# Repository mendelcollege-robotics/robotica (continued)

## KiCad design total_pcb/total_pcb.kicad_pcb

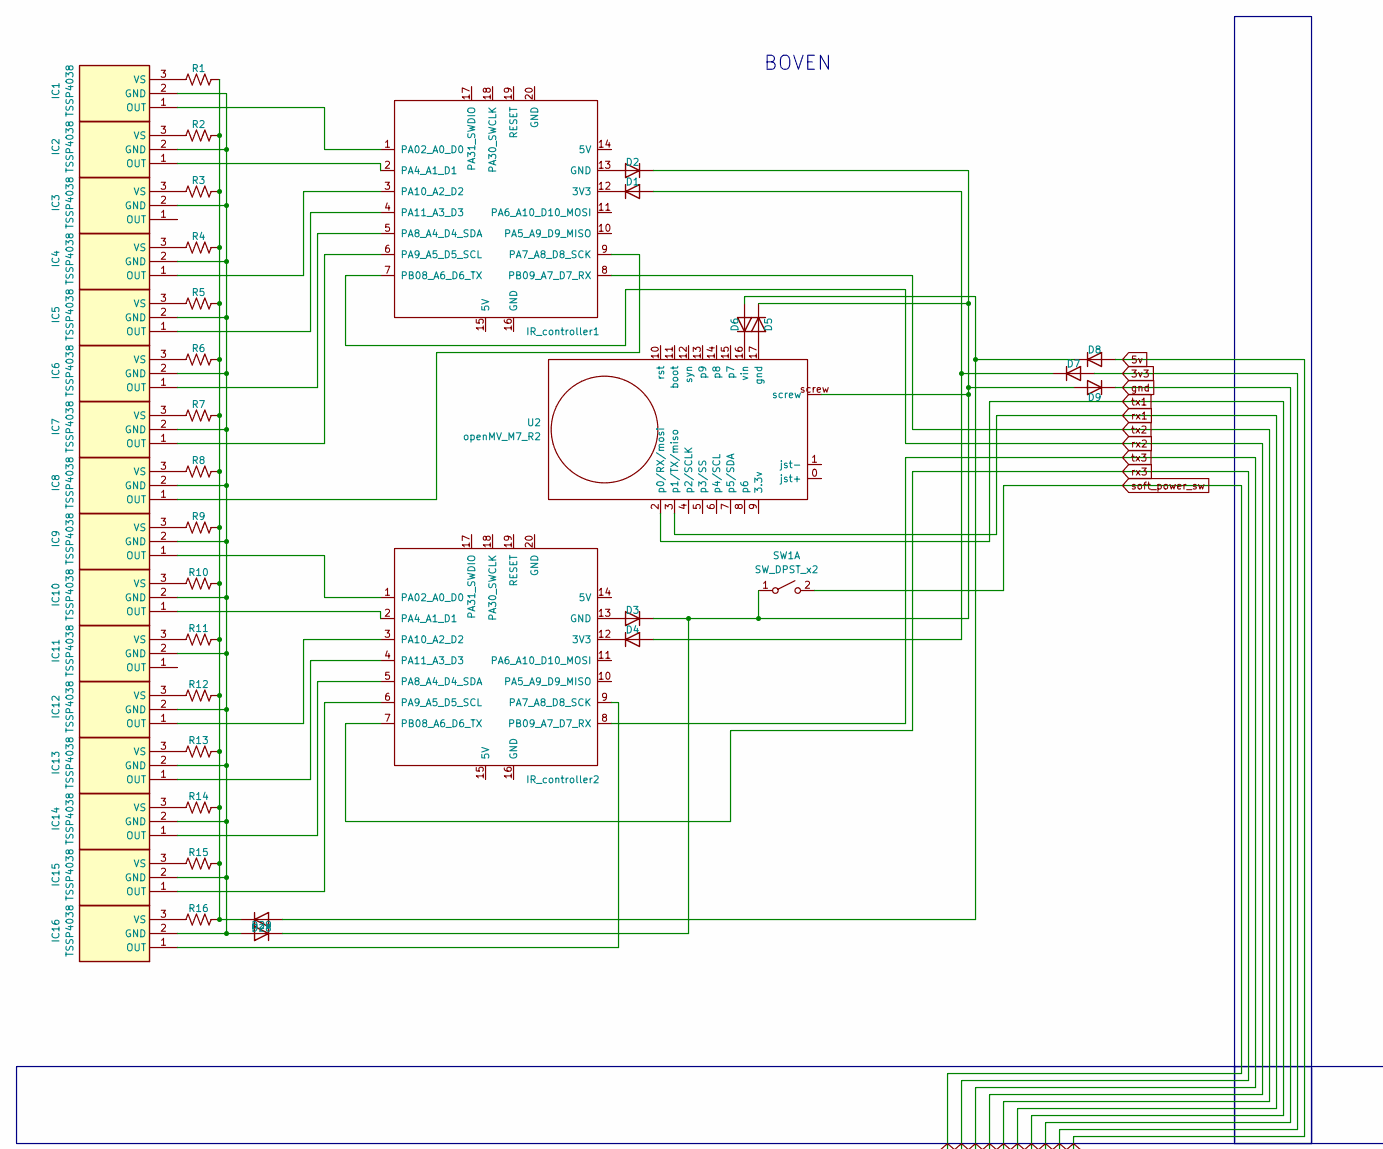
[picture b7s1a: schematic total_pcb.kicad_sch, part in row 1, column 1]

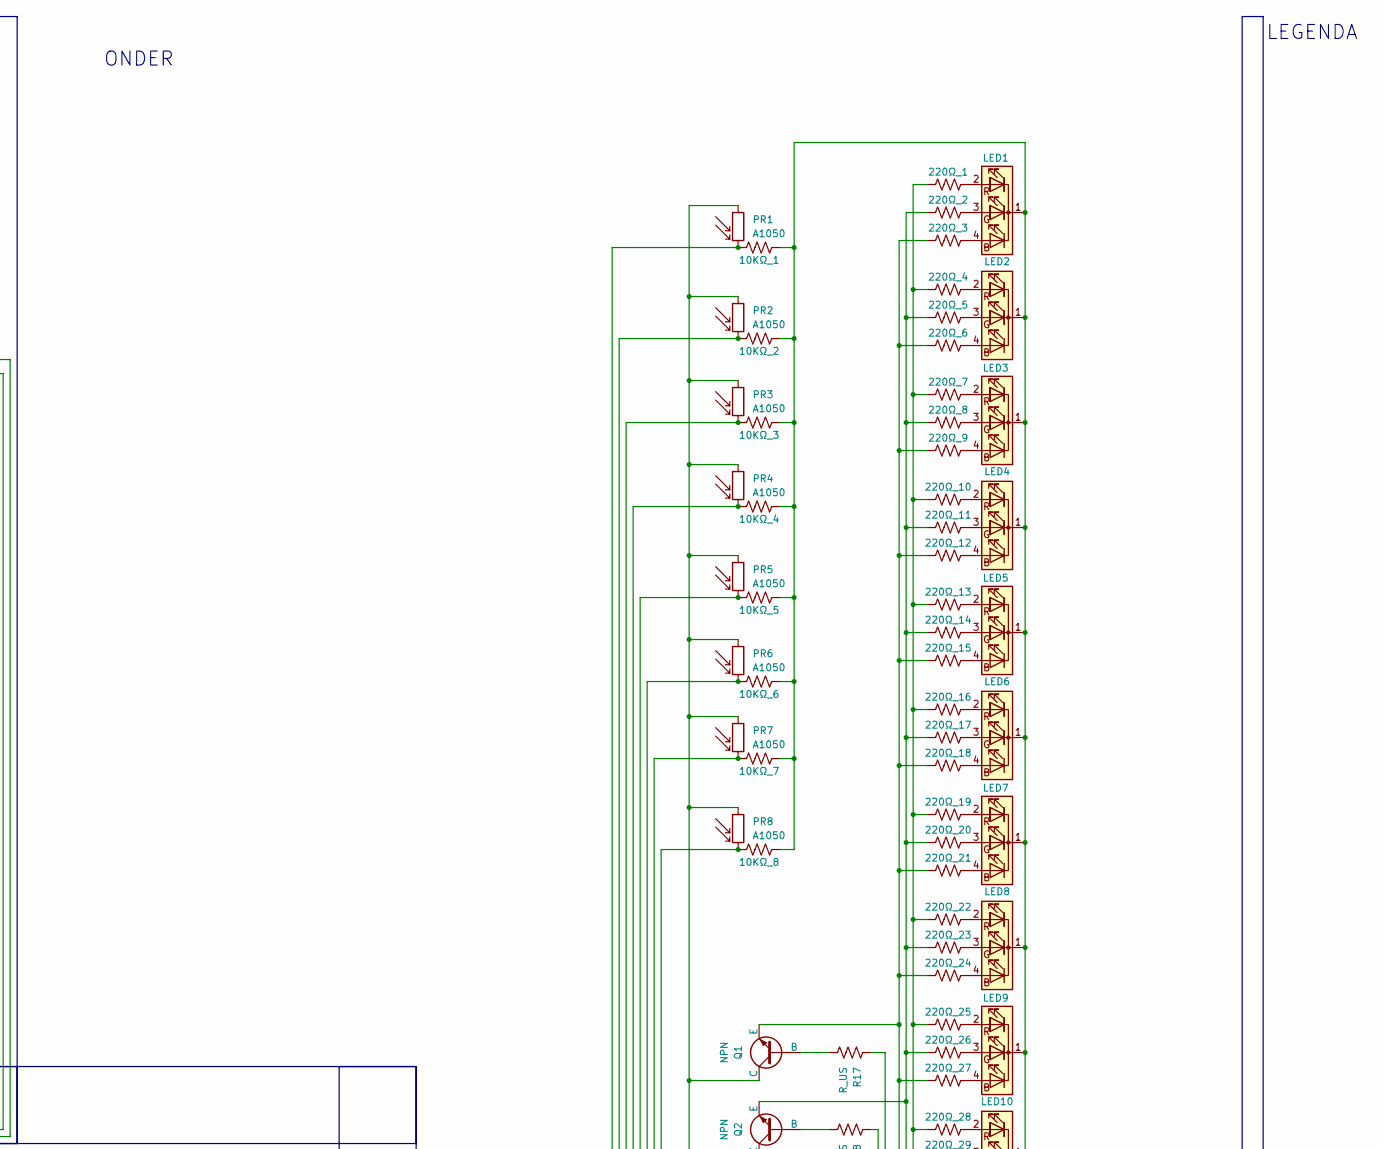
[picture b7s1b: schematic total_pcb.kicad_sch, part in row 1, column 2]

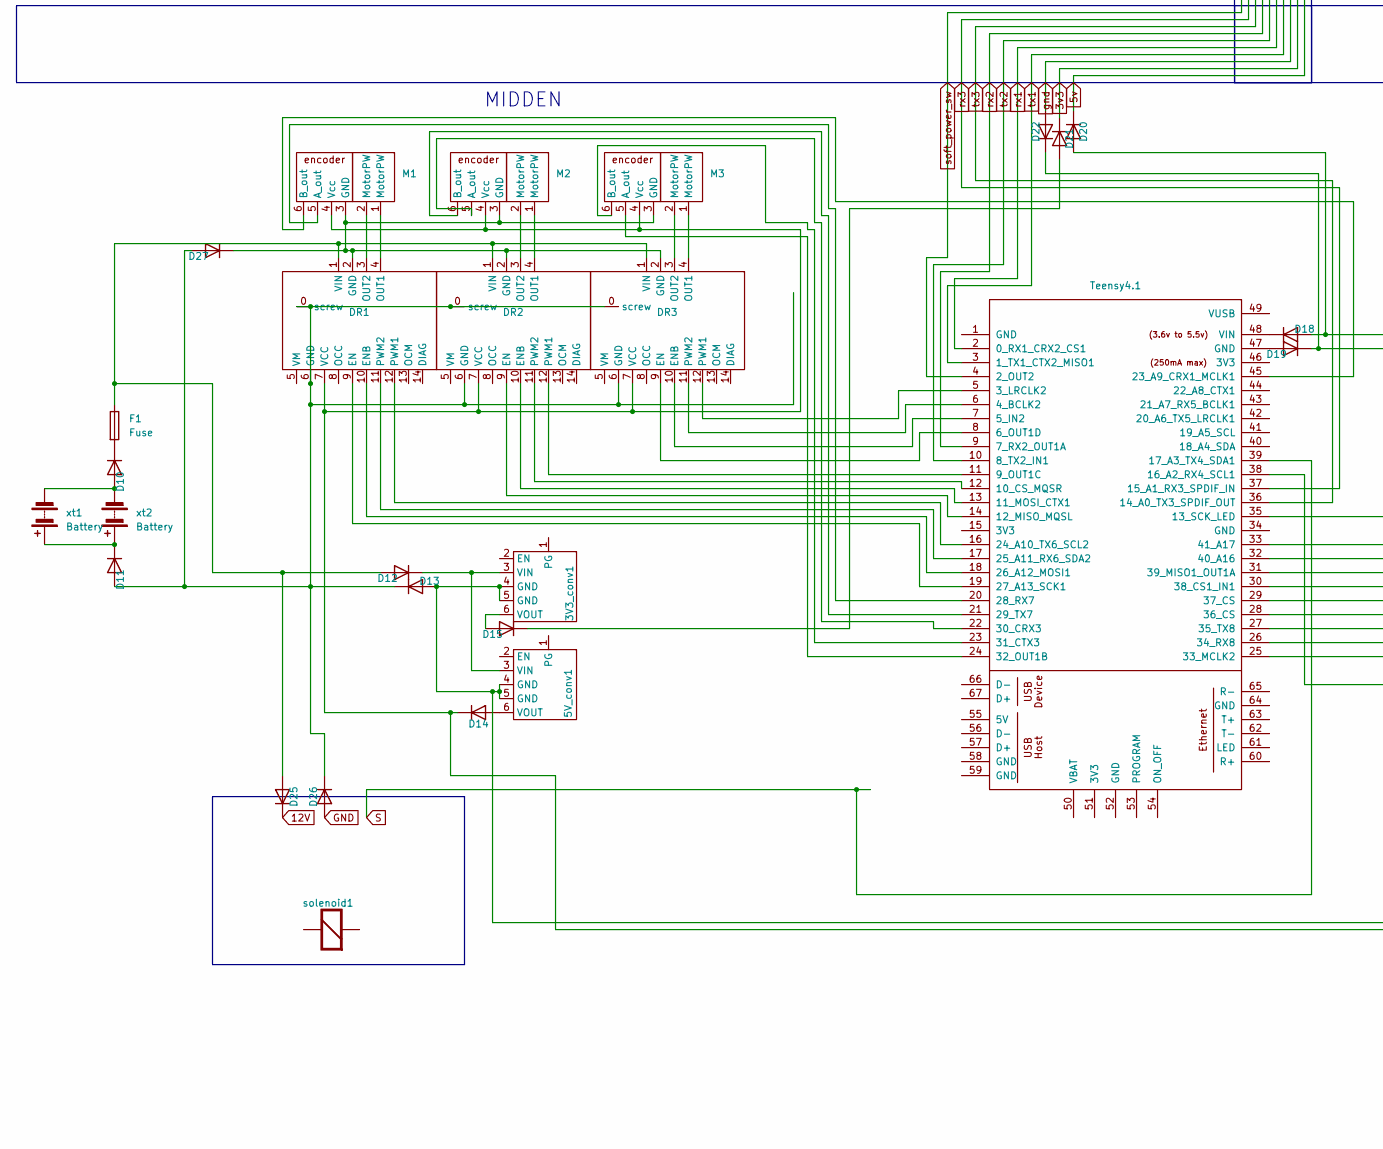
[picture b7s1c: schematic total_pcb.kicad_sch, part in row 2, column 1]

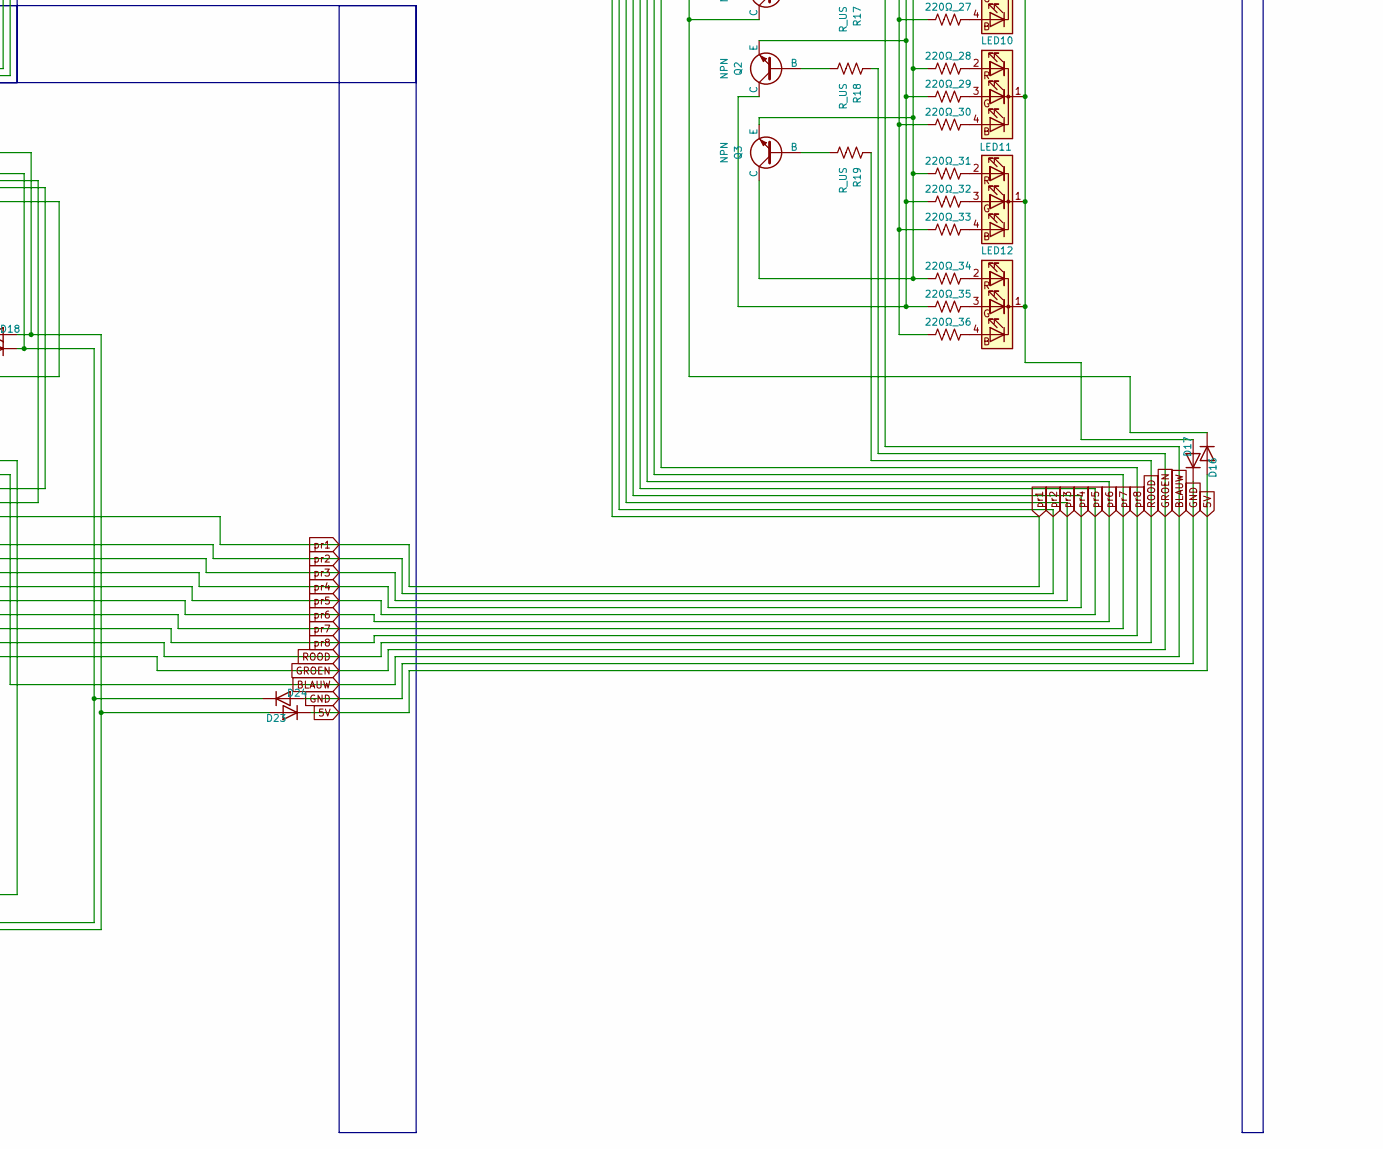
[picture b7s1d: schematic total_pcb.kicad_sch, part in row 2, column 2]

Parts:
3V3_conv1, 5V_conv1: pololu-U1V10F5
10KΩ_1, 10KΩ_2, 10KΩ_3, 10KΩ_4, 10KΩ_5, 10KΩ_6, 10KΩ_7, 10KΩ_8, 220Ω_1, 220Ω_2, 220Ω_3, 220Ω_4, 220Ω_5, 220Ω_6, 220Ω_7, 220Ω_8, 220Ω_9, 220Ω_10, 220Ω_11, 220Ω_12, 220Ω_13, 220Ω_14, 220Ω_15, 220Ω_16, 220Ω_17, 220Ω_18, 220Ω_19, 220Ω_20, 220Ω_21, 220Ω_22, 220Ω_23, 220Ω_24, 220Ω_25, 220Ω_26, 220Ω_27, 220Ω_28, 220Ω_29, 220Ω_30, 220Ω_31, 220Ω_32, 220Ω_33, 220Ω_34, 220Ω_35, 220Ω_36: R_US; R_Axial_DIN0207_L6.3mm_D2.5mm_P10.16mm_Horizontal
D1, D2, D3, D4, D5, D6, D7, D8, D9, D10, D11, D12, D13, D14, D15, D16, D17, D18, D19, D20, D21, D22, D23, D24, D25, D26, D27, D28, D29: D; D_MELF-RM10_Universal_Handsoldering
DR1, DR2, DR3: TB9051FTG
F1: Fuse; Fuseholder_TR5_Littelfuse_No560_No460
IC1, IC2, IC3, IC4, IC5, IC6, IC7, IC8, IC9, IC10, IC11, IC12, IC13, IC14, IC15, IC16: TSSP4038; Manufacturer_Part_Number TSSP4038; Mouser Part Number 782-TSSP4038
IR_controller1, IR_controller2: Seeed Studio XIAO SAMD21; XIAO-SAMD21-RP2040-14P-2.54-21X17.8MM (Seeeduino XIAO)
LED1, LED2, LED3, LED4, LED5, LED6, LED7, LED8, LED9, LED10, LED11, LED12: LED_KRGB; LED_D5.0mm-4_RGB_Wide_Pins
M1, M2, M3: PinHeader_1x06_P1.27mm_Vertical
PR1, PR2, PR3, PR4, PR5, PR6, PR7, PR8: A1050; R_LDR_D6.4mm_P3.4mm_Vertical
Q1, Q2, Q3: NPN
R1, R2, R3, R4, R5, R6, R7, R8, R9, R10, R11, R12, R13, R14, R15, R16, R17, R18, R19: R_US; R_Axial_DIN0207_L6.3mm_D2.5mm_P10.16mm_Horizontal
SW1: SW_DPST_x2
U2: openMV_M7_R2; openmv_m7_r2
solenoid1: Re; Rating V/Ω
teensy1: Teensy4.1; Teensy41
xt1: Battery; AMASS_XT60-F_1x02_P7.20mm_Vertical
xt2: Battery; AMASS_XT30U-M_1x02_P5.0mm_Vertical

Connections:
3v3: D7.2 (A), D21.1 (K)
5V: D16.2 (A), D23.1 (K)
5v: D8.2 (A), D20.1 (K)
12V: D25.1 (K)
BLAUW: R17.2, teensy1.38 (16_A2_RX4_SCL1)
GND: D17.1 (K), D24.2 (A), D26.2 (A)
GROEN: R18.2, teensy1.25 (33_MCLK2)
unnamed: 3V3_conv1.3 (VIN), 5V_conv1.3 (VIN), D12.1 (K)
unnamed: 3V3_conv1.6 (VOUT), D15.2 (A)
unnamed: 5V_conv1.6 (VOUT), D14.2 (A)
unnamed: D1.2 (A), D4.2 (A), D7.1 (K)
unnamed: D1.1 (K), IR_controller1.12 (3V3)
unnamed: D2.2 (A), IR_controller1.13 (GND)
unnamed: D2.1 (K), D3.1 (K), D5.1 (K), D9.2 (A), D29.1 (K), SW1.1 (A), U2.screw
unnamed: D3.2 (A), IR_controller2.13 (GND)
unnamed: D4.1 (K), IR_controller2.12 (3V3)
unnamed: D5.2 (A), U2.17 (gnd)
unnamed: D6.1 (K), U2.16 (vin)
unnamed: D10.2 (A), xt1.2 (-), xt2.2 (-)
unnamed: D10.1 (K), F1.2
unnamed: D11.2 (A), D13.1 (K), D26.1 (K), D27.2 (A), DR1.0 (screw), DR1.6 (GND), DR2.0 (screw), DR2.6 (GND), DR3.0 (screw), DR3.6 (GND)
unnamed: D11.1 (K), xt1.1 (+), xt2.1 (+)
unnamed: D12.2 (A), D25.2 (A), DR1.1 (VIN), DR2.1 (VIN), DR3.1 (VIN), F1.1
unnamed: 3V3_conv1.4 (GND), 3V3_conv1.5 (GND), 5V_conv1.4 (GND), 5V_conv1.5 (GND), D13.2 (A), D19.1 (K), D22.1 (K), D24.1 (K)
unnamed: D14.1 (K), D18.2 (A), D20.2 (A), D23.2 (A), DR1.7 (VCC), DR2.7 (VCC), DR3.7 (VCC), M1.4 (Vcc), M2.4 (Vcc), M3.4 (Vcc)
unnamed: D15.1 (K), D21.2 (A)
unnamed: D16.1 (K), PR1.1, PR2.1, PR3.1, PR4.1, PR5.1, PR6.1, PR7.1, PR8.1, Q1.1 (C)
unnamed: 10KΩ_1.2, 10KΩ_2.2, 10KΩ_3.2, 10KΩ_4.2, 10KΩ_5.2, 10KΩ_6.2, 10KΩ_7.2, 10KΩ_8.2, D17.2 (A), LED1.1 (K), LED2.1 (K), LED3.1 (K), LED4.1 (K), LED5.1 (K), LED6.1 (K), LED7.1 (K), LED8.1 (K), LED9.1 (K), LED10.1 (K), LED11.1 (K), LED12.1 (K)
unnamed: D18.1 (K), teensy1.48 (VIN)
unnamed: D19.2 (A), teensy1.47 (GND)
unnamed: D27.1 (K), DR1.2 (GND), DR2.2 (GND), DR3.2 (GND), M1.3 (GND), M2.3 (GND), M3.3 (GND)
unnamed: D6.2 (A), D8.1 (K), D28.2 (A)
unnamed: D28.1 (K), R1.2, R2.2, R3.2, R4.2, R5.2, R6.2, R7.2, R8.2, R9.2, R10.2, R11.2, R12.2, R13.2, R14.2, R15.2, R16.2
unnamed: D29.2 (A), IC1.2 (GND), IC2.2 (GND), IC3.2 (GND), IC4.2 (GND), IC5.2 (GND), IC6.2 (GND), IC7.2 (GND), IC8.2 (GND), IC9.2 (GND), IC10.2 (GND), IC11.2 (GND), IC12.2 (GND), IC13.2 (GND), IC14.2 (GND), IC15.2 (GND), IC16.2 (GND)
unnamed: DR1.9 (EN), teensy1.19 (27_A13_SCK1)
unnamed: DR1.10 (ENB), teensy1.18 (26_A12_MOSI1)
unnamed: DR1.4 (OUT1), M1.1 (MotorPW)
unnamed: DR1.3 (OUT2), M1.2 (MotorPW)
unnamed: DR1.12 (PWM1), teensy1.16 (24_A10_TX6_SCL2)
unnamed: DR1.11 (PWM2), teensy1.17 (25_A11_RX6_SDA2)
unnamed: DR2.9 (EN), teensy1.14 (12_MISO_MQSL)
unnamed: DR2.10 (ENB), teensy1.13 (11_MOSI_CTX1)
unnamed: DR2.4 (OUT1), M2.1 (MotorPW)
unnamed: DR2.3 (OUT2), M2.2 (MotorPW)
unnamed: DR2.12 (PWM1), teensy1.11 (9_OUT1C)
unnamed: DR2.11 (PWM2), teensy1.12 (10_CS_MQSR)
unnamed: DR3.9 (EN), teensy1.8 (6_OUT1D)
unnamed: DR3.10 (ENB), teensy1.7 (5_IN2)
unnamed: DR3.4 (OUT1), M3.1 (MotorPW)
unnamed: DR3.3 (OUT2), M3.2 (MotorPW)
unnamed: DR3.12 (PWM1), teensy1.5 (3_LRCLK2)
unnamed: DR3.11 (PWM2), teensy1.6 (4_BCLK2)
unnamed: IC1.1 (OUT), IR_controller1.1 (PA02_A0_D0)
unnamed: IC1.3 (VS), R1.1
unnamed: IC2.1 (OUT), IR_controller1.2 (PA4_A1_D1)
unnamed: IC2.3 (VS), R2.1
unnamed: IC3.3 (VS), R3.1
unnamed: IC4.1 (OUT), IR_controller1.3 (PA10_A2_D2)
unnamed: IC4.3 (VS), R4.1
unnamed: IC5.1 (OUT), IR_controller1.4 (PA11_A3_D3)
unnamed: IC5.3 (VS), R5.1
unnamed: IC6.1 (OUT), IR_controller1.5 (PA8_A4_D4_SDA)
unnamed: IC6.3 (VS), R6.1
unnamed: IC7.1 (OUT), IR_controller1.6 (PA9_A5_D5_SCL)
unnamed: IC7.3 (VS), R7.1
unnamed: IC8.1 (OUT), IR_controller1.9 (PA7_A8_D8_SCK)
unnamed: IC8.3 (VS), R8.1
unnamed: IC9.1 (OUT), IR_controller2.1 (PA02_A0_D0)
unnamed: IC9.3 (VS), R9.1
unnamed: IC10.1 (OUT), IR_controller2.2 (PA4_A1_D1)
unnamed: IC10.3 (VS), R10.1
unnamed: IC11.3 (VS), R11.1
unnamed: IC12.1 (OUT), IR_controller2.3 (PA10_A2_D2)
unnamed: IC12.3 (VS), R12.1
unnamed: IC13.1 (OUT), IR_controller2.4 (PA11_A3_D3)
unnamed: IC13.3 (VS), R13.1
unnamed: IC14.1 (OUT), IR_controller2.5 (PA8_A4_D4_SDA)
unnamed: IC14.3 (VS), R14.1
unnamed: IC15.1 (OUT), IR_controller2.6 (PA9_A5_D5_SCL)
unnamed: IC15.3 (VS), R15.1
unnamed: IC16.1 (OUT), IR_controller2.9 (PA7_A8_D8_SCK)
unnamed: IC16.3 (VS), R16.1
unnamed: 220Ω_3.1, LED1.4 (BA)
unnamed: 220Ω_2.1, LED1.3 (GA)
unnamed: 220Ω_1.1, LED1.2 (RA)
unnamed: 220Ω_6.1, LED2.4 (BA)
unnamed: 220Ω_5.1, LED2.3 (GA)
unnamed: 220Ω_4.1, LED2.2 (RA)
unnamed: 220Ω_9.1, LED3.4 (BA)
unnamed: 220Ω_8.1, LED3.3 (GA)
unnamed: 220Ω_7.1, LED3.2 (RA)
unnamed: 220Ω_12.1, LED4.4 (BA)
unnamed: 220Ω_11.1, LED4.3 (GA)
unnamed: 220Ω_10.1, LED4.2 (RA)
unnamed: 220Ω_15.1, LED5.4 (BA)
unnamed: 220Ω_14.1, LED5.3 (GA)
unnamed: 220Ω_13.1, LED5.2 (RA)
unnamed: 220Ω_18.1, LED6.4 (BA)
unnamed: 220Ω_17.1, LED6.3 (GA)
unnamed: 220Ω_16.1, LED6.2 (RA)
unnamed: 220Ω_21.1, LED7.4 (BA)
unnamed: 220Ω_20.1, LED7.3 (GA)
unnamed: 220Ω_19.1, LED7.2 (RA)
unnamed: 220Ω_24.1, LED8.4 (BA)
unnamed: 220Ω_23.1, LED8.3 (GA)
unnamed: 220Ω_22.1, LED8.2 (RA)
unnamed: 220Ω_27.1, LED9.4 (BA)
unnamed: 220Ω_26.1, LED9.3 (GA)
unnamed: 220Ω_25.1, LED9.2 (RA)
unnamed: 220Ω_30.1, LED10.4 (BA)
unnamed: 220Ω_29.1, LED10.3 (GA)
unnamed: 220Ω_28.1, LED10.2 (RA)
unnamed: 220Ω_33.1, LED11.4 (BA)
unnamed: 220Ω_32.1, LED11.3 (GA)
unnamed: 220Ω_31.1, LED11.2 (RA)
unnamed: 220Ω_36.1, LED12.4 (BA)
unnamed: 220Ω_35.1, LED12.3 (GA)
unnamed: 220Ω_34.1, LED12.2 (RA)
unnamed: M1.5 (A_out), teensy1.20 (28_RX7)
unnamed: M1.6 (B_out), teensy1.45 (23_A9_CRX1_MCLK1)
unnamed: M2.5 (A_out), teensy1.22 (30_CRX3)
unnamed: M2.6 (B_out), teensy1.21 (29_TX7)
unnamed: M3.5 (A_out), teensy1.24 (32_OUT1B)
unnamed: M3.6 (B_out), teensy1.23 (31_CTX3)
unnamed: Q1.2 (B), R17.1
unnamed: 220Ω_3.2, 220Ω_6.2, 220Ω_9.2, 220Ω_12.2, 220Ω_15.2, 220Ω_18.2, 220Ω_21.2, 220Ω_24.2, 220Ω_27.2, 220Ω_30.2, 220Ω_33.2, 220Ω_36.2, Q1.3 (E)
unnamed: Q2.2 (B), R18.1
unnamed: 220Ω_2.2, 220Ω_5.2, 220Ω_8.2, 220Ω_11.2, 220Ω_14.2, 220Ω_17.2, 220Ω_20.2, 220Ω_23.2, 220Ω_26.2, 220Ω_29.2, 220Ω_32.2, 220Ω_35.2, Q2.1 (C), Q2.3 (E)
unnamed: Q3.2 (B), R19.1
unnamed: 220Ω_1.2, 220Ω_4.2, 220Ω_7.2, 220Ω_10.2, 220Ω_13.2, 220Ω_16.2, 220Ω_19.2, 220Ω_22.2, 220Ω_25.2, 220Ω_28.2, 220Ω_31.2, 220Ω_34.2, Q3.1 (C), Q3.3 (E)
ROOD: R19.2, teensy1.26 (34_RX8)
S: teensy1.39 (17_A3_TX4_SDA1)
gnd: D9.1 (K), D22.2 (A)
pr1: 10KΩ_1.1, PR1.2, teensy1.35 (13_SCK_LED)
pr2: 10KΩ_2.1, PR2.2, teensy1.33 (41_A17)
pr3: 10KΩ_3.1, PR3.2, teensy1.32 (40_A16)
pr4: 10KΩ_4.1, PR4.2, teensy1.31 (39_MISO1_OUT1A)
pr5: 10KΩ_5.1, PR5.2, teensy1.30 (38_CS1_IN1)
pr6: 10KΩ_6.1, PR6.2, teensy1.29 (37_CS)
pr7: 10KΩ_7.1, PR7.2, teensy1.28 (36_CS)
pr8: 10KΩ_8.1, PR8.2, teensy1.27 (35_TX8)
rx1: U2.3 (p1/TX/miso), teensy1.2 (0_RX1_CRX2_CS1)
rx2: IR_controller1.7 (PB08_A6_D6_TX), teensy1.9 (7_RX2_OUT1A)
rx3: IR_controller2.7 (PB08_A6_D6_TX), teensy1.37 (15_A1_RX3_SPDIF_IN)
soft_power_sw: SW1.2 (B), teensy1.4 (2_OUT2)
tx1: U2.2 (p0/RX/mosi), teensy1.3 (1_TX1_CTX2_MISO1)
tx2: IR_controller1.8 (PB09_A7_D7_RX), teensy1.10 (8_TX2_IN1)
tx3: IR_controller2.8 (PB09_A7_D7_RX), teensy1.36 (14_A0_TX3_SPDIF_OUT)

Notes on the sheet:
BOVEN
MIDDEN
LEGENDA
ONDER

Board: 2 copper layers, 143 parts (0 on the bottom side), 140 nets, no tracks yet.

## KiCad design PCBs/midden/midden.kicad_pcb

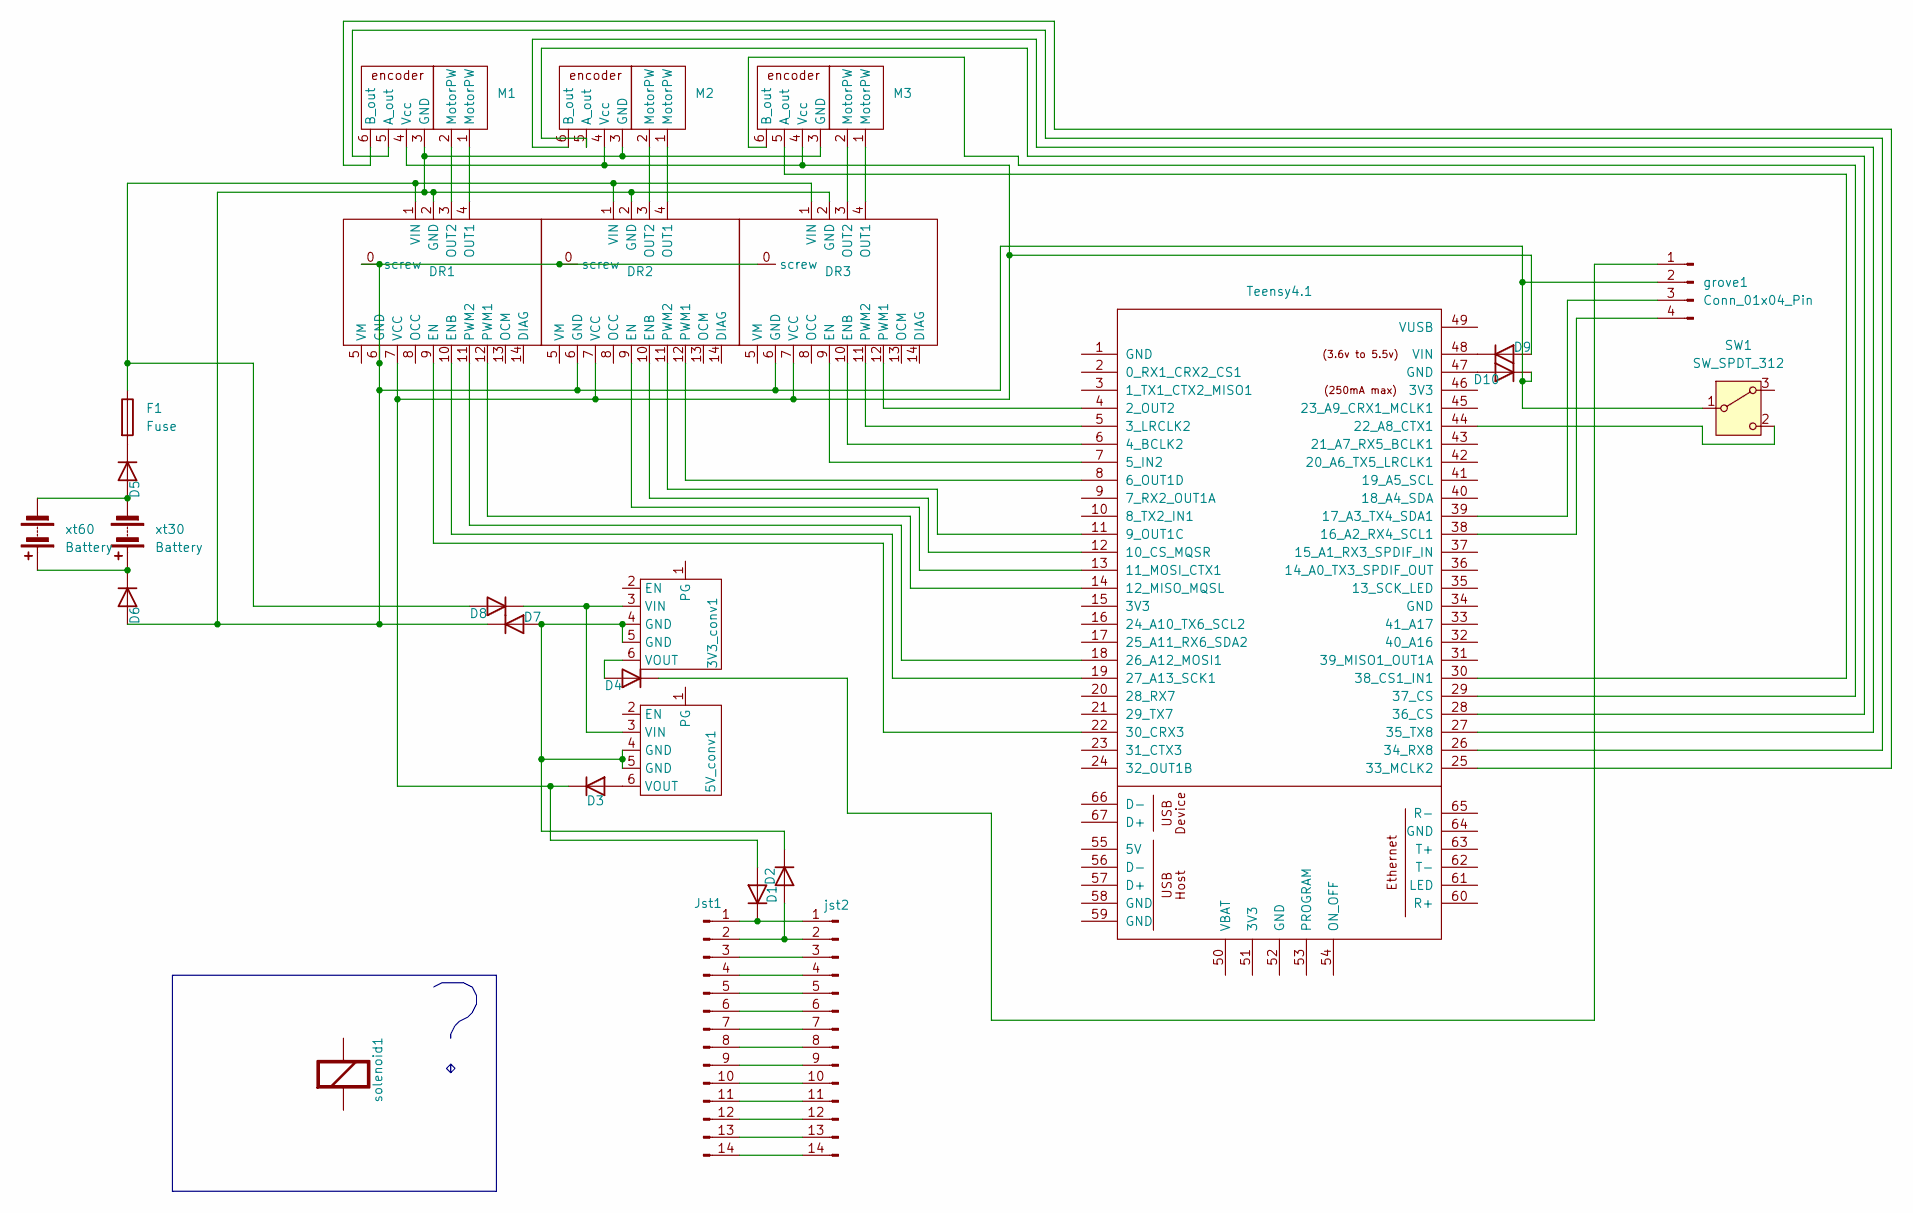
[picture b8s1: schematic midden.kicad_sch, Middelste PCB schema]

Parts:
3V3_conv1, 5V_conv1: pololu_power_converter
D1, D2, D3, D4, D5, D6, D7, D8, D9, D10: D; D_MELF-RM10_Universal_Handsoldering
DR1, DR2, DR3: TB9051FTG
F1: Fuse; Fuseholder_TR5_Littelfuse_No560_No460
Jst1: Conn_01x14_Pin; JST_EH_B14B-EH-A_1x14_P2.50mm_Vertical
M1, M2, M3: pololu_4.41 Metal Gearmotor 25Dx63L mm MP 12V with 48 CPR E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
SW1: SW_SPDT_312
grove1: Conn_01x04_Pin; NS-Tech_Grove_1x04_P2mm_Vertical
jst2: Conn_01x14_Pin; JST_EH_S14B-EH_1x14_P2.50mm_Horizontal
solenoid1: Re; Rating V/Ω
teensy1: Teensy4.1; TEENSY41
xt30: Battery; AMASS_XT30U-M_1x02_P5.0mm_Vertical
xt60: Battery; AMASS_XT60-F_1x02_P7.20mm_Vertical

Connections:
unnamed: 3V3_conv1.3 (VIN), 5V_conv1.3 (VIN), D8.1 (K)
unnamed: 3V3_conv1.6 (VOUT), D4.2 (A)
unnamed: 5V_conv1.6 (VOUT), D3.2 (A)
unnamed: D1.2 (A), D3.1 (K), D9.2 (A), DR1.7 (VCC), DR2.7 (VCC), DR3.7 (VCC), M1.4 (Vcc), M2.4 (Vcc), M3.4 (Vcc)
unnamed: D1.1 (K), Jst1.1, jst2.1
unnamed: D2.2 (A), Jst1.2, jst2.2
unnamed: 3V3_conv1.4 (GND), 3V3_conv1.5 (GND), 5V_conv1.4 (GND), 5V_conv1.5 (GND), D2.1 (K), D7.2 (A)
unnamed: D4.1 (K), grove1.1
unnamed: D5.2 (A), xt30.2 (-), xt60.2 (-)
unnamed: D5.1 (K), F1.2
unnamed: D6.1 (K), xt30.1 (+), xt60.1 (+)
unnamed: D8.2 (A), DR1.1 (VIN), DR2.1 (VIN), DR3.1 (VIN), F1.1
unnamed: D9.1 (K), teensy1.48 (VIN)
unnamed: D10.2 (A), teensy1.47 (GND)
unnamed 15: D6.2 (A), D7.1 (K), D10.1 (K), DR1.0 (screw), DR1.2 (GND), DR1.6 (GND), DR2.0 (screw), DR2.2 (GND), DR2.6 (GND), DR3.0 (screw), DR3.2 (GND), DR3.6 (GND), M1.3 (GND), M2.3 (GND), M3.3 (GND), SW1.1 (B), grove1.2; also elsewhere on the board
unnamed: DR1.9 (EN), teensy1.22 (30_CRX3)
unnamed: DR1.10 (ENB), teensy1.19 (27_A13_SCK1)
unnamed: DR1.4 (OUT1), M1.1 (MotorPW)
unnamed: DR1.3 (OUT2), M1.2 (MotorPW)
unnamed: DR1.12 (PWM1), teensy1.14 (12_MISO_MQSL)
unnamed: DR1.11 (PWM2), teensy1.18 (26_A12_MOSI1)
unnamed: DR2.9 (EN), teensy1.13 (11_MOSI_CTX1)
unnamed: DR2.10 (ENB), teensy1.12 (10_CS_MQSR)
unnamed: DR2.4 (OUT1), M2.1 (MotorPW)
unnamed: DR2.3 (OUT2), M2.2 (MotorPW)
unnamed: DR2.12 (PWM1), teensy1.8 (6_OUT1D)
unnamed: DR2.11 (PWM2), teensy1.11 (9_OUT1C)
unnamed: DR3.9 (EN), teensy1.7 (5_IN2)
unnamed: DR3.10 (ENB), teensy1.6 (4_BCLK2)
unnamed: DR3.4 (OUT1), M3.1 (MotorPW)
unnamed: DR3.3 (OUT2), M3.2 (MotorPW)
unnamed: DR3.12 (PWM1), teensy1.4 (2_OUT2)
unnamed: DR3.11 (PWM2), teensy1.5 (3_LRCLK2)
unnamed: Jst1.3, jst2.3
unnamed: Jst1.4, jst2.4
unnamed: Jst1.5, jst2.5
unnamed: Jst1.6, jst2.6
unnamed: Jst1.7, jst2.7
unnamed: Jst1.8, jst2.8
unnamed: Jst1.9, jst2.9
unnamed: Jst1.10, jst2.10
unnamed: Jst1.11, jst2.11
unnamed: Jst1.12, jst2.12
unnamed: Jst1.13, jst2.13
unnamed: Jst1.14, jst2.14
unnamed: M1.5 (A_out), teensy1.26 (34_RX8)
unnamed: M1.6 (B_out), teensy1.25 (33_MCLK2)
unnamed: M2.5 (A_out), teensy1.28 (36_CS)
unnamed: M2.6 (B_out), teensy1.27 (35_TX8)
unnamed: M3.5 (A_out), teensy1.30 (38_CS1_IN1)
unnamed: M3.6 (B_out), teensy1.29 (37_CS)
unnamed: SW1.2 (C), teensy1.44 (22_A8_CTX1)
unnamed: grove1.3, teensy1.39 (17_A3_TX4_SDA1)
unnamed: grove1.4, teensy1.38 (16_A2_RX4_SCL1)

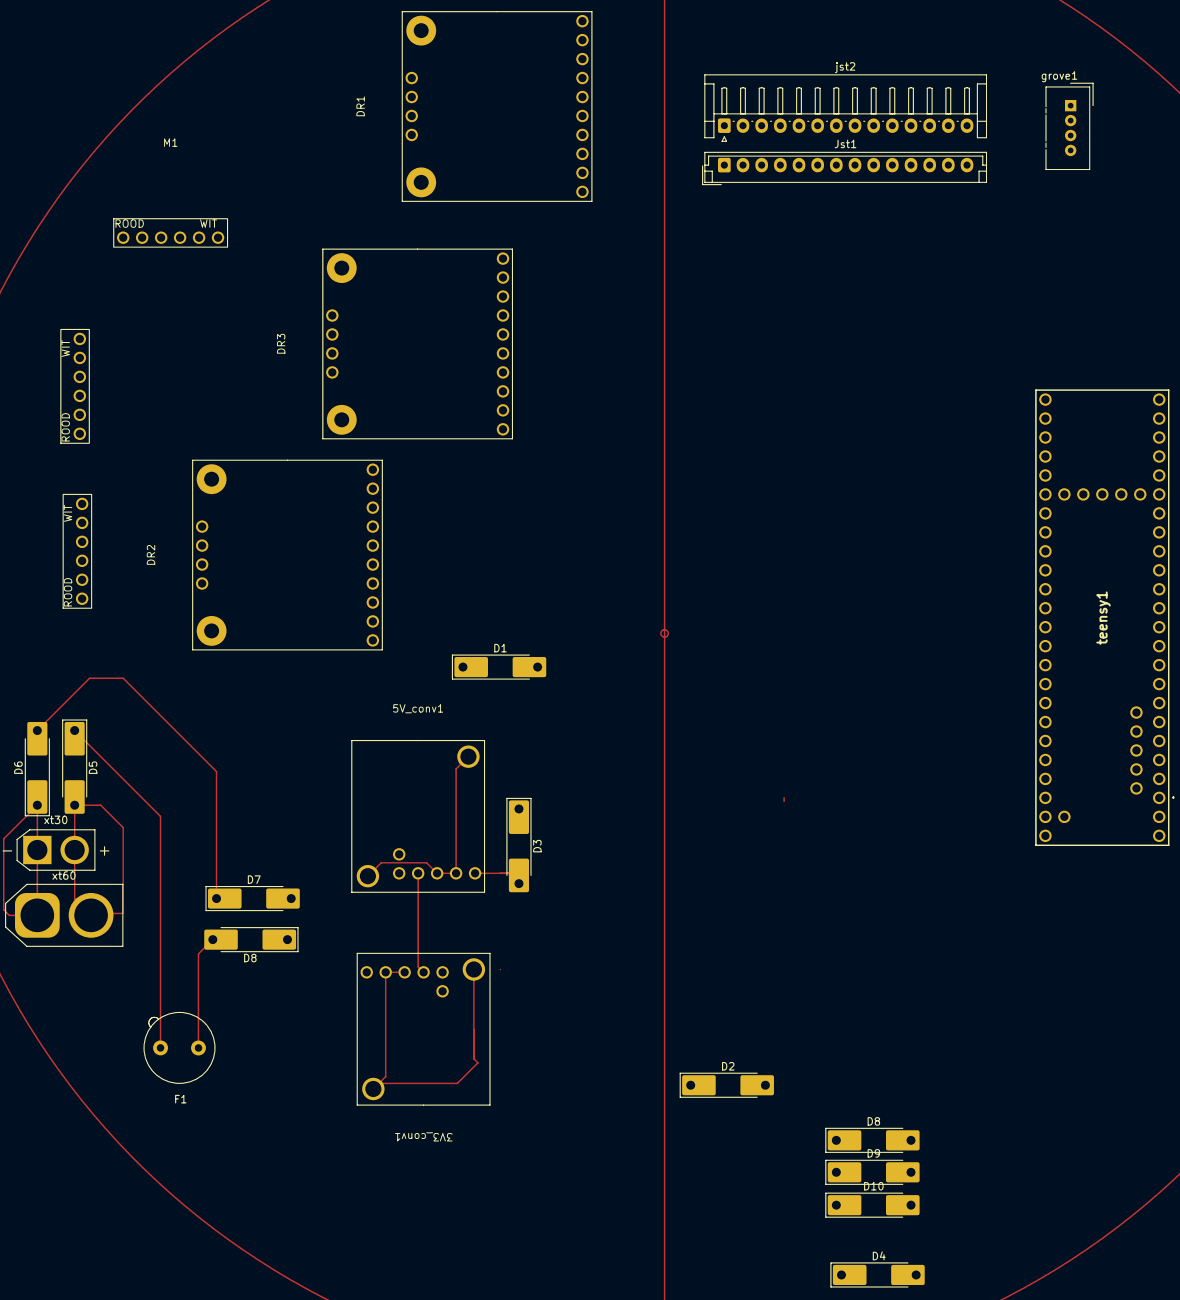
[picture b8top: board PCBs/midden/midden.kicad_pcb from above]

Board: 2 copper layers, 26 parts (0 on the bottom side), 53 nets.

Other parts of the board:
D8#2: D; D_MELF-RM10_Universal_Handsoldering

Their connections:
unnamed 15: D8#2.2 (A); also elsewhere on the board

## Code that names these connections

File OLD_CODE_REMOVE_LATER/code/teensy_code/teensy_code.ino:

#include <TimerThree.h>
#include <Arduino.h>

int speed = 1000; // speed 0-1

volatile int PWMval1 = 0;   // PWM value 0-100
volatile int PWMval2 = 0;   // PWM value 0-100
volatile int PWMval3 = 0;   // PWM value 0-100

int incomingbyte1 = 0;  //the byte that it is reciefing
bool iswriting1 = false;  //true if writing else fals
String tlocdat1 = "";  //temporary location data
String locdat1 = "";   //location data
int nir1 = "-99"; // which ir sensor it is
int pir1 = "-99"; // amount of pulses it had

int incomingbyte2 = 0;  //same but for seeed xiao N 2
bool iswriting2 = false;
String tlocdat2 = ""; 
String locdat2 = ""; 
int nir2 = "-99";
int pir2 = "-99";

float degwhere = -99.0; // where the ball is in degrees

int led = 13;

int m1enA = 6;
int m1enB = 5;
int m1pwm1 = 4;
int m1pwm2 = 3;
int m1encoA = 32;
int m1encoB = 31;

int m2enA = 12;
int m2enB = 11;
int m2pwm1 = 9;
int m2pwm2 = 10;
int m2encoA = 30;
int m2encoB = 29;

int m3enA = 27;
int m3enB = 26;
int m3pwm1 = 24;
int m3pwm2 = 25;
int m3encoA = 28;
int m3encoB = 23;

int softpwr = 2;

int pr1 = 13;
int pr2 = 41;
int pr3 = 40;
int pr4 = 39;
int pr5 = 38;
int pr6 = 37;
int pr7 = 36;
int pr8 = 35;

int dpr1 = "LOW";
int dpr2 = "LOW";
int dpr3 = "LOW";
int dpr4 = "LOW";
int dpr5 = "LOW";
int dpr6 = "LOW";
int dpr7 = "LOW";
int dpr8 = "LOW";

double sp1 = 0.00;
double sp2 = 0.00;
double sp3 = 0.00;

void setup() {
  pinMode(m1enA, OUTPUT);
  pinMode(m1enB, OUTPUT);
  pinMode(m1pwm1, OUTPUT);
  pinMode(m1pwm2, OUTPUT);
  
  pinMode(m2enA, OUTPUT);
  pinMode(m2enB, OUTPUT);
  pinMode(m2pwm1, OUTPUT);
  pinMode(m2pwm2, OUTPUT);
  
  pinMode(m3enA, OUTPUT);
  pinMode(m3enB, OUTPUT);
  pinMode(m3pwm1, OUTPUT);
  pinMode(m3pwm2, OUTPUT);

  pinMode(softpwr, INPUT_PULLUP);

  pinMode(pr1, INPUT);
  pinMode(pr2, INPUT);
  pinMode(pr3, INPUT);
  pinMode(pr4, INPUT);
  pinMode(pr5, INPUT);
  pinMode(pr6, INPUT);
  pinMode(pr7, INPUT);
  pinMode(pr8, INPUT);

  Serial.begin(9600);
  Serial3.begin(9600);
  Serial2.begin(9600);

  Timer3.initialize(800); // 800 microseconds / 1.25kHz
  Timer3.attachInterrupt(updatePWM); 
}

void updatePWM() {
  static int counter = 0;

  if (counter < PWMval1) {
    digitalWrite(m1enA, HIGH);
  } else {
    digitalWrite(m1enA, LOW);
  }
  
  if (counter < PWMval2) {
    digitalWrite(m2enA, HIGH);
  } else {
    digitalWrite(m2enA, LOW);
  }
  
  if (counter < PWMval3) {
    digitalWrite(m3enA, HIGH);
  } else {
    digitalWrite(m3enA, LOW);
  }

  counter++;
  if (counter >= 100) {
    counter = 0;
  }
}

void mcpsoftpwm1(int value1) {
  if (value1 < 0) value1 = 0;
  if (value1 > 100) value1 = 100;

  Serial.print("softPWM pin: enA, value: ");
  Serial.println(value1); 
  PWMval1 = value1; 
}
void mcpsoftpwm2(int value2) {
  if (value2 < 0) value2 = 0;
  if (value2 > 100) value2 = 100;

  Serial.print("softPWM pin: enA, value: ");
  Serial.println(value2); 
  PWMval2 = value2; 
}void mcpsoftpwm3(int value3) {
  if (value3 < 0) value3 = 0;
  if (value3 > 100) value3 = 100;

  Serial.print("softPWM pin: enA, value: ");
  Serial.println(value3); 
  PWMval3 = value3; 
}

void move1(int sped1) {
  sp1 = abs(sped1)*0.1;
  mcpsoftpwm1(sp1);
  digitalWrite(m1enB, LOW);
  if (sped1 < 0) {
    Serial.print("back ");
    digitalWrite(m1pwm1, LOW);
    digitalWrite(m1pwm2, HIGH);
  } else {
    Serial.print("forward ");
    digitalWrite(m1pwm1, HIGH);
    digitalWrite(m1pwm2, LOW);
  } 
  Serial.println(sp1);
}

void move2(int sped2) {
  sp2 = abs(sped2)*0.1;
  mcpsoftpwm2(sp2);
  digitalWrite(m2enB, LOW);
  if (sped2 < 0) {
    Serial.print("back ");
    digitalWrite(m2pwm1, LOW);
    digitalWrite(m2pwm2, HIGH);
  } else {
    Serial.print("forward ");
    digitalWrite(m2pwm1, HIGH);
    digitalWrite(m2pwm2, LOW);
  } 
  Serial.println(sp2);
}

void move3(int sped3) {
  sp3 = abs(sped3)*0.1;
  mcpsoftpwm3(sp3);
  digitalWrite(m3enB, LOW);
  if (sped3 < 0) {
    Serial.print("back ");
    digitalWrite(m3pwm1, LOW);
    digitalWrite(m3pwm2, HIGH);
  } else {
    Serial.print("forward ");
    digitalWrite(m3pwm1, HIGH);
    digitalWrite(m3pwm2, LOW);
  } 
  Serial.println(sp3);
}


void drive(int speeeed, int direction){
 //
 // Direction............|.Motor 1.|.Motor 2.|.Motor 3.
 // 0deg(forward)........|....0....|....-....|....+....
 // 60deg................|....+....|....-....|....0....    
 // 120deg...............|....+....|....0....|....-....
 // 180 deg (backward)...|....0....|....+....|....-.... 
 // 240 deg..............|....-....|....+....|....0....
 // 300 deg..............|....-....|....0....|....+....
 //
 if(direction>330 || direction<=30){
    //0 deg
    //Serial.println("drive 0 deg"); 
    move1(0);
    move2(-speeeed);
    move3(speeeed);
  }else if (direction>30 && direction <= 90){
    //60 deg
    //Serial.println("drive 60deg");
    move1(speeeed);
    move2(-speeeed);
    move3(0);
  }else if (direction>90 && direction <= 150){
    //120 deg
    //Serial.println("drive 120 deg");
    move1(speeeed);
    move2(0);
    move3(-speeeed);
  }else if (direction > 150 && direction <= 210) {
    //180 degrees
    //Serial.println("drive  180 deg");
    move1(0);
    move2(speeeed);
    move3(-speeeed);
  }else if (direction > 210 && direction <= 270) {
    //240 degrees
    //Serial.println("drive 240 deg");
    move1(-speeeed);
    move2(speeeed);
    move3(0);
  }else if (direction > 270 && direction <= 330) {
    //300 degrees
    //Serial.println("drive 300 deg");
    move1(-speeeed);
    move2(0);
    move3(speeeed);
  }else{
    Serial.println("how?");  
  }
}

void loop() {
  int sprst = digitalRead(softpwr);  //softpower status
  if(sprst == LOW){
    dpr1 = digitalRead(pr1);
    dpr2 = digitalRead(pr2); 
    dpr3 = digitalRead(pr3); 
    dpr4 = digitalRead(pr4); 
    dpr5 = digitalRead(pr5); 
    dpr6 = digitalRead(pr6); 
    dpr7 = digitalRead(pr7); 
    dpr8 = digitalRead(pr8); 
  
    if(dpr1 == HIGH){
      //go back to ?deg
    }else if (dpr2 == HIGH){
      //go back to ?deg
    }else if (dpr3 == HIGH){
      //go back to ?deg
    }else if (dpr4 == HIGH){
      //go back to ?deg
    }else if (dpr5 == HIGH){
      //go back to ?deg
    }else if (dpr6 == HIGH){
      //go back to ?deg
    }else if (dpr7 == HIGH){
      //go back to ?deg
    }else if (dpr8 == HIGH){
      //go back to ?deg
    }else{
      if (Serial3.available() > 0) {
        incomingbyte1 = Serial3.read();
        //Serial.print(char(incomingbyte1));
        if (incomingbyte1 == 's'){
          iswriting1 = true;
          tlocdat1 = "";
        }else if(incomingbyte1 == 'e'){
          iswriting1 = false;
          locdat1 = tlocdat1;        
        }else if(iswriting1 == true){
          //Serial.print(char(incomingbyte1));
          tlocdat1 += (char)incomingbyte1;  
        }
      }
      if (Serial2.available() > 0) {
        incomingbyte2 = Serial2.read();
        //Serial.print(char(incomingbyte2));
        if (incomingbyte2 == 's'){
          iswriting2 = true;
          tlocdat2 = "";
        }else if(incomingbyte1 == 'e'){
          iswriting2 = false;
          locdat2 = tlocdat1;        
        }else if(iswriting2 == true){
          //Serial.print(char(incomingbyte1));
          tlocdat2 += (char)incomingbyte1;  
        }
      }
      //Serial.println(locdat);
      sscanf(locdat1.c_str(), "%d, %d", &nir1, &pir1);
      sscanf(locdat2.c_str(), "%d, %d", &nir2, &pir2);

      Serial.print("locdat: ");
      Serial.print(String(locdat1));
      Serial.println(String(locdat2));
      
      
      if(pir1 > pir2){
         if(nir1 = 1){    //not good looking code because posbile wrong wireing
          degwhere = 0;      
         }else if(nir1 = 2){
          degwhere = 22.5;
         }else if(nir1 = 3){
          degwhere = 45;
         }else if(nir1 = 4){
          degwhere = 67.5;
         }else if(nir1 = 5){
          degwhere = 90;
         }else if(nir1 = 6){
          degwhere = 112.5;
         }else if(nir1 = 7){
          degwhere = 135;
         }else if(nir1 = 8){
          degwhere = 157.5;
         }
      }else{     
         if(nir2 = 1){
          degwhere = 180;
         }else if(nir2 = 2){
          degwhere = 202.5;
         }else if(nir2 = 3){
          degwhere = 225;
         }else if(nir2 = 4){
          degwhere = 247.5;
         }else if(nir2 = 5){
          degwhere = 270;
         }else if(nir2 = 6){
          degwhere = 292.5;
         }else if(nir2 = 7){
          degwhere = 315; 
         }else if(nir2 = 8){
          degwhere = 337.5; 
         }
      }

      Serial.print("Ball is at ");
      Serial.print(degwhere);
      Serial.println(" degrees.");
      drive(75, degwhere);
      delay(1);
    }
  }else{
    Serial.println("softPWR is off, waiting");
    delay(100);  
  }
}
